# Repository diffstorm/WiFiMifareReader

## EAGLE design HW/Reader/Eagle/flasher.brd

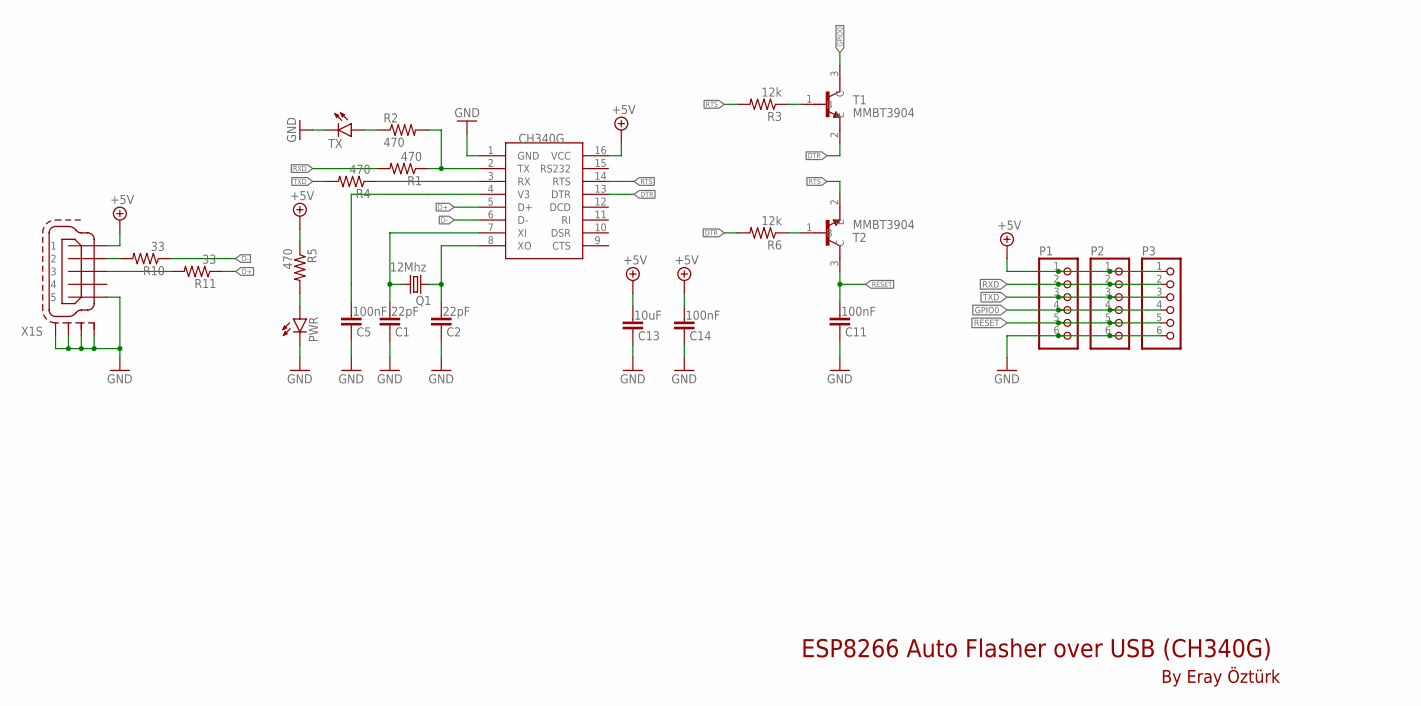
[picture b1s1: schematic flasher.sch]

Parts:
C1, C2: 22pF; C0805
C5, C11, C14: 100nF; C0805
C13: 10uF; C0805
P1, P2, P3: PINHD-1X6; 1X06
PWR: LEDCHIP-LED0805; CHIP-LED0805
Q1: 12Mhz; HC49/S
R1, R2, R4, R5: 470; M0805
R3, R6: 12k; M0805
R10, R11: 33; M0805
T1, T2: MMBT3904; SOT95P240X120-3N
TX: LEDCHIP-LED0805; CHIP-LED0805
U1: CH340G; SOIC16
X1: MINI-USB-SCHIELD-32005-201; 32005-201

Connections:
+5V: C13.2, C14.2, P1.1, P2.1, P3.1, R5.1, U1.16 (VCC), X1.1
D+: R11.1, U1.5 (D+)
D-: R10.1, U1.6 (D-)
DTR: R6.2, T1.2 (E), U1.13 (DTR)
GND: C1.1, C2.1, C5.1, C11.1, C13.1, C14.1, P1.6, P2.6, P3.6, PWR.C, TX.C, U1.1 (GND), X1.5, X1.M1 (S1), X1.M2 (S2), X1.M3 (S3), X1.M4 (S4)
GPIO0: P1.4, P2.4, P3.4, T1.3 (C)
unnamed: R1.1, R2.2, U1.2 (TX)
unnamed: R4.1, U1.3 (RX)
unnamed: PWR.A, R5.2
unnamed: R2.1, TX.A
unnamed: R3.1, T1.1 (B)
unnamed: R6.1, T2.1 (B)
unnamed: R10.2, X1.2
unnamed: R11.2, X1.3
unnamed: C5.2, U1.4 (V3)
unnamed: C1.2, Q1.1, U1.7 (XI)
unnamed: C2.2, Q1.2, U1.8 (XO)
RESET: C11.2, P1.5, P2.5, P3.5, T2.3 (C)
RTS: R3.2, T2.2 (E), U1.14 (RTS)
RXD: P1.2, P2.2, P3.2, R1.2
TXD: P1.3, P2.3, P3.3, R4.2

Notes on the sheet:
ESP8266 Auto Flasher over USB (CH340G)
By Eray Öztürk

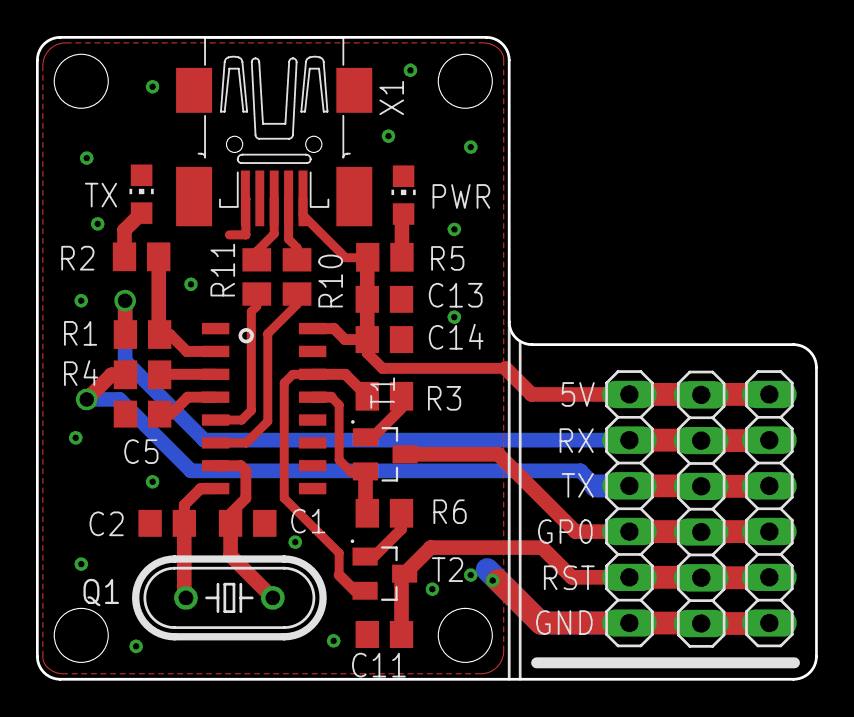
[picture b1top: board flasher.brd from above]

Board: 2 copper layers, 43.3 x 35.7 mm, 24 parts (0 on the bottom side), 21 nets.

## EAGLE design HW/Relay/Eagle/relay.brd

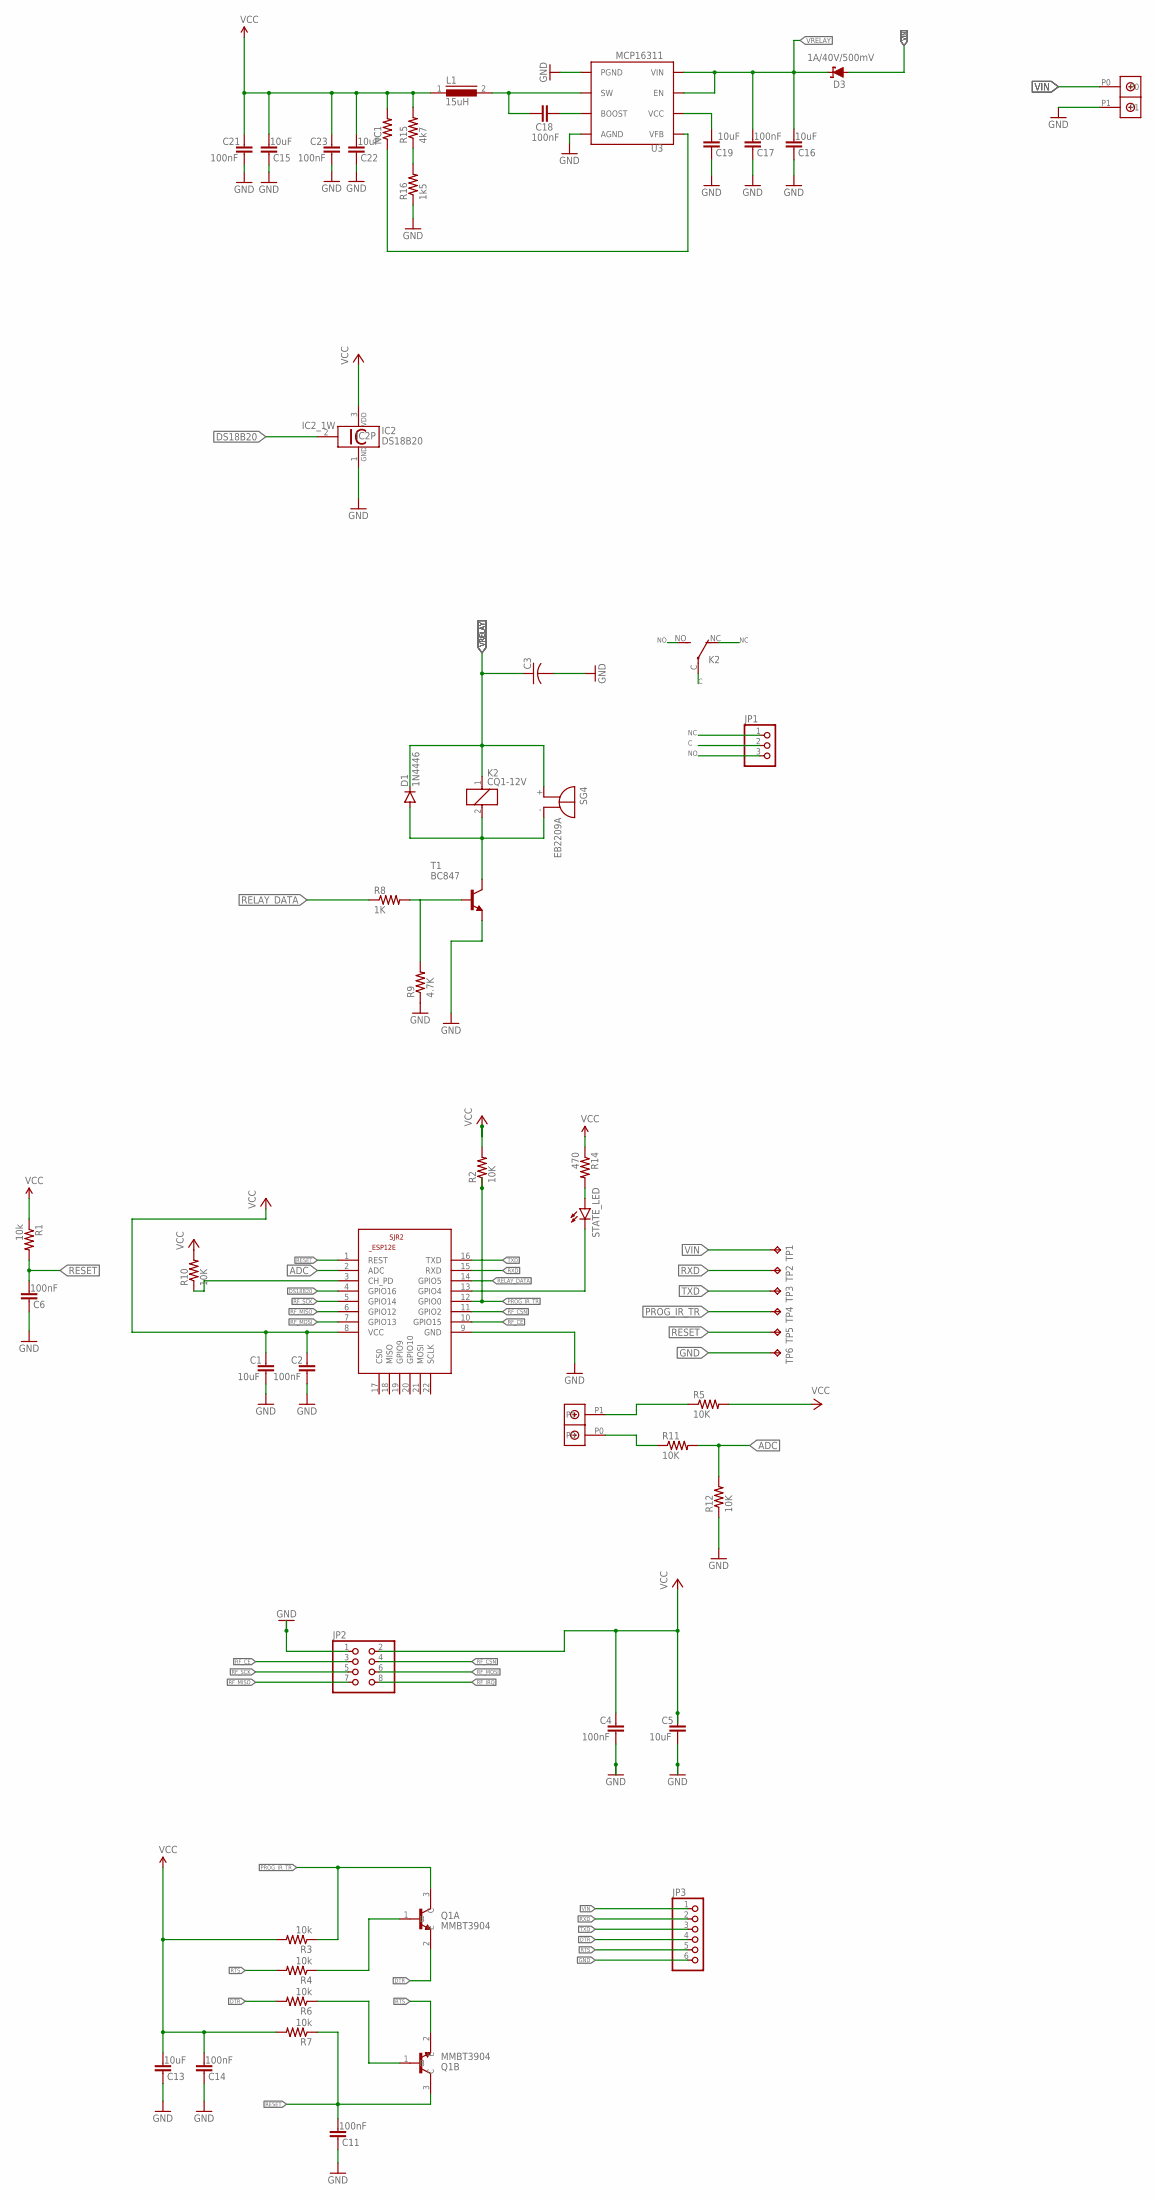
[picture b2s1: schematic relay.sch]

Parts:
C1, C5, C13, C15, C16, C19, C22: 10uF; C0805
C2, C4, C6, C11, C14, C17, C18, C21, C23: 100nF; C0805
C3: C-US050-025X075; C050-025X075
D1: 1N4446; DO35-10
D3: 1A/40V/500mV; SMA-DIODE
IC2: DS18B20; TO92-
JP1: PINHD-1X3; 1X03
JP2: PINHD-2X4; 2X04
JP3: PINHD-1X6; 1X06
K2: CQ1-12V; CQ1
L1: 15uH; DR74
NC1: SPARKFUN_RESISTOR0805-RES; SPARKFUN_0805
Q1A, Q1B: MMBT3904; SOT95P240X120-3N
R1, R3, R4, R6, R7: 10k; SPARKFUN_0805
R2, R5, R10, R11, R12: 10K; M2012
R8: 1K; M2012
R9: 4.7K; M2012
R14: 470; SPARKFUN_0805
R15: 4k7; SPARKFUN_0805
R16: 1k5; SPARKFUN_0805
SG4: EB2209A
SJR2: ESP8266-12EESP12E; ESP8266-ESP12E
STATE_LED: LED3MM
T1: BC847; SOT23
TP1, TP2, TP3, TP4, TP5, TP6: TPTP20SQ; TP20SQ
U3: MCP16311; MSOP8
U$1, U$2: DBCONN-1X2

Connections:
ADC: R11.2, R12.2, SJR2.2 (ADC)
C: JP1.2, K2.C
DS18B20: IC2.2 (1W), SJR2.4 (GPIO16)
DTR: JP3.4, Q1A.2 (E), R6.2
GND: C1.2, C2.2, C3.2, C4.2, C5.2, C6.1, C11.1, C13.1, C14.1, C15.1, C16.1, C17.1, C19.1, C21.2, C22.1, C23.2, IC2.1 (GND), JP2.1, JP3.6, R9.1, R12.1, R16.1, SJR2.9 (GND), T1.2 (E), TP6.TP, U3.AGND, U3.PGND, U$1.P1
unnamed: R8.2, R9.2, T1.1 (B)
unnamed: Q1A.1 (B), R4.1
unnamed: NC1.1, U3.VFB
unnamed: R14.2, STATE_LED.A
unnamed: D1.A, K2.2, SG4.-, T1.3 (C)
unnamed: Q1B.1 (B), R6.1
unnamed: R5.1, U$2.P1
unnamed: R11.1, U$2.P0
unnamed: C18.2, L1.2, U3.SW
unnamed: C18.1, U3.BOOST
unnamed: C19.2, U3.VCC
unnamed: R15.1, R16.2
unnamed: R10.1, SJR2.3 (CH_PD)
NC: JP1.1, K2.NC (O)
NO: JP1.3, K2.NO (S)
PROG_IR_TR: Q1A.3 (C), R2.1, R3.1, SJR2.12 (GPIO0), TP4.TP
RELAY_DATA: R8.1, SJR2.14 (GPIO5)
RESET: C6.2, C11.2, Q1B.3 (C), R1.2, R7.1, SJR2.1 (REST), TP5.TP
RF_CE: JP2.3, SJR2.10 (GPIO15)
RF_CSN: JP2.4, SJR2.11 (GPIO2)
RF_IRQ: JP2.8
RF_MISO: JP2.7, SJR2.6 (GPIO12)
RF_MOSI: JP2.6, SJR2.7 (GPIO13)
RF_SCK: JP2.5, SJR2.5 (GPIO14)
RTS: JP3.5, Q1B.2 (E), R4.2
RXD: JP3.2, SJR2.15 (RXD), TP2.TP
RXD1: SJR2.13 (GPIO4), STATE_LED.K (C)
TXD: JP3.3, SJR2.16 (TXD), TP3.TP
VCC: C1.1, C2.1, C4.1, C5.1, C13.2, C14.2, C15.2, C21.1, C22.2, C23.1, IC2.3 (VDD), JP2.2, L1.1, NC1.2, R1.1, R2.2, R3.2, R5.2, R7.2, R10.2, R14.1, R15.2, SJR2.8 (VCC)
VIN: D3.A, JP3.1, TP1.TP, U$1.P0
VRELAY: C3.1, C16.2, C17.2, D1.C, D3.C, K2.1, SG4.+, U3.EN, U3.VIN

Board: 2 copper layers, 56 parts (0 on the bottom side), 35 nets, no tracks yet.

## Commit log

2020-03-03 Create directories
2020-03-04 Add files via upload
    Upload version1
2020-03-04 test
2020-03-09 led ve buzzer eklendi
2020-03-09 led ve buzzer duzenlemeleri yapildi
2020-03-09 ledpinleri tanımlandı
2020-03-09 timer duzeltildi
2020-03-10 SysTimer adding for led and buzzer
2020-03-10 led and buzzer solved
2020-03-11 Add files via upload
    Malzeme Listesi ve IR led dökümanları eklendi.
2020-03-12 eagle schematic is uploaded
    Eagle sch. documents only included reader and programmable part of first step.
2020-03-13 Create Libraries
2020-03-28 [Docs] Add initial config details
2020-03-28 Delete v1.0
    swap files with latest update v1.1
2020-03-28 swap files with lastest update v1.1
2020-03-28 WiFiReaderConfig - Add relay comm method
2020-03-28 Reader v1.1 schema png. version added.
2020-03-28 Relay_config dosyası oluşturuldu.
2020-03-28 RelayConfig Değişti
2020-03-29 Relay_Card
2020-03-29 Add libs, code format, improve docs, add card structs
2020-03-29 add visitor and guard cards options
2020-03-30 master a güncel include dosyaları eklendi
2020-03-31 Add tools.cpp for tool functions
2020-03-31 Add types.h for generic types
2020-03-31 Remove rar files
2020-03-31 Add CardConfig
2020-03-31 Code format
2020-04-02 [Card] Add Card API, CardConfig and tools, types, defs
2020-04-02 deleted old version of programming sch.
2020-04-02 deleted version of door_locks v1.1 sch.
2020-04-02 wifi_reader, program_reader sch. is changed
    Programlama pinleri değiştirildi, eklendi. door_lock_v1.2.sch üzerinde hatalar düzeltildir. Footprintler kontrol edildi.
2020-04-02 Minor improvements on schematic
2020-04-02 Add setters and helper functions into Card API
2020-04-02 Add Scheduler library
2020-04-03 relay_sch updated.
    Relay sch, Programming sch, sch. image are updated.
2020-04-03 deleting relay.pro
    not usable for now.
2020-04-03 Delete relay.brd
    Not prepared for now
2020-04-03 Add DeviceConfig
2020-04-03 Update relay.sch
    NRF24L01 module has changed.
2020-04-04 Add datasheets
2020-04-04 Code clean up
2020-04-05 Add DeviceConfig API
2020-04-06 filesystem kütüphanesi oluşturuldu
2020-04-06 Replace DateTime_t based time variables with UTC ones
2020-04-07 [Fix] Bugfix on Read/Write into card sectors
2020-04-07 WriteBlock function is written to Reader Library
2020-04-08 ReadBlock function is written to Reader Library
2020-04-08 manual
2020-04-08 RTC library
    RTC yazma ve okuma fonksiyonları yazıldı.
2020-04-09 RTC
    RTC memory e yazma ve okuma fonksiyonları tek struct üzerinden olacak şekilde revize edildi.
2020-04-09 Relay schematic improved
2020-04-09 Add Compress API, minor code improvements
2020-04-09 RTC time
    RTC memory'e time bilgisi yazma ve okuma fonksiyonları yazıldı.
2020-04-09 Fix WiFi Config
2020-04-10 Reader Library
    Reader library has been edited.
2020-04-11 Schematics are updated
    Kickstart flasher PCB
2020-04-12 Flasher CH340G SCH & PCB
2020-04-13 Flasher Update
2020-04-13 filesystem and whitelist
2020-04-14 RTC update time
    RTC memory alanına ntp den çekilen güncel saati deep sleep süresi eklenerek yazan fonksiyon eklendi.
2020-04-16 RTC time record
    RTC de tutulan zaman bilgisinin mili saniye türünden hesaplanarak güncellenmesi için örnek kod yazıldı.
2020-04-17 filesystem ve whitelist
    Whitelist daha fail safe yapılmadı. Testlerde calıstığı görüldü. (Testler detaylı yapılmadı).
2020-04-17 gözden kaçmış
2020-04-17 tools include edildi
    tools include edip crc fonksi,yonunu ve tablosunu sildim. Ayrı dosyada çalışttıgım için crc yi kopyalamıştım
2020-04-19 hata
2020-04-19 whitelist
    update fonksiyonu Whitelist için ihtiyaç doğrultusunda tekrar yazıldı
2020-04-19 kesilen dosya hatası giderildi
2020-04-19 rtc
    rtc fonksiyonları güncellendi
2020-04-21 reader lib update
    reader test
2020-04-21 fileSystem güncellendi
    Konuşulan değişiklikler yapıldı. Yorumlar eklendi. update güncellendi. Sistemde kalan boş alanı bulan fonk. yazıldı.
2020-04-21 fonksiyonlara loglar eklendi
2020-04-23 whitelist update
    Testleri yaptım delete fonksiyonunda sorun var. Üzerinde çalışıyorum
2020-04-23 Reader lib update
    Reader lib update
2020-04-25 whitelist tamamlandı
    Daha detaylı test edildikten sonra, serialprintler yerine debuglog kullanılıp, yorumları yazılacak
2020-04-27 Debug log improved. Use LOGp as printf
    IR disabled
    duplicated example functions renamed
2020-04-29 whitelist
2020-04-29 fs wl
2020-04-29 conflict resolved
2020-04-29 Tidy up
2020-04-29 Remove trash files
2020-04-29 Update gitignore
2020-05-03 Add placeholders for Protocol and Parser
2020-05-16 UDP and NTP
    test edildi

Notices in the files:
parts and their libraries:
SparkFun-DiscreteSemi: Licensing: Creative Commons ShareAlike 4.0 International - https://creativecommons.org/licenses/by-sa/4.0
